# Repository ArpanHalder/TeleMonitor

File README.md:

# TeleMonitor
This Open Hardware initiative is focused mostly on industrial application. In fact, this started with designing a low-cost Telemonitoring system for Mining Industry Applications. It is an embedded data transmission setup made up on small Arduino like boards. For long distance communication between device nodes, it uses RS-485

![alt text][master_diag]

##Motivation
While working in the laboratory, our team did experiment similar thing using state of the art services. However, not every educational institute has access to premium facilities. This project is initiated to enable us (who have access to premium education) to build some full-scale copyleft open technology that can be used for demonstration of remote monitoring operation in academia as well as in industries.
(After the device, hopefully soon the projects for IDE of this instrument, and Open Source Analytics & Visualization tools for this project shall be published after development of first working prototype.)

##Design Approaches
One of the primary objectives is keeping the hardware cheap, straightforward and reparable. We don't want a design where if one component fails the whole circuit is replaced, which create extra junk on the surface of the earth.

###This Device is motivated by the idea of "Democratisation of Technology & Education."
<https://en.wikipedia.org/wiki/Democratization_of_technology>

<http://www.thehindu.com/news/national/andhra-pradesh/science-should-touch-lives-of-common-people/article8539013.ece>

This is why we wish to keep the design simple and affordable like DIY projects, however, rich with all necessary features. This we can hopefully achieve by the cognitive support of the community. We also suggest restricting use of components in the design that tier III nations cannot afford to import or implement in the industries. 

##Ways to Contribute in this project

Discuss the possible improvement, and feature requirements.

Contact : tech.halder.arpan@gmail.com

[master_diag]: https://github.com/ArpanHalder/TeleMonitor/blob/master/Hardware/Schimatics/Schematic%20Diagram%20V1.png

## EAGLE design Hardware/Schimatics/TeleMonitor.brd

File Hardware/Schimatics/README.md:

#Hardware Schematics for Telemonitoring nodes

![alt text][master_diag]

## How to Read/Open

The files are made with eagle cad. 

There are image files naming  *.PNG  

Currently Schematics is drawn in a way which can easily be implimented with one sided perforated board. (to avoid PCB printing cost for early developers.) 

**Please Note:** the top layer on PCB (the red streaks) need not to be solder bridged, rather a thin wire may be used which shall be soldered on bottom side.

![alt text][master_pcb]

### Current Job
~~Looking forward to make a vias less PCB that can be printed and fabricated manually.~~

~~On Veroboard~~

Add more necessary components and rearrangement for improvements. 

[master_diag]: https://github.com/ArpanHalder/TeleMonitor/blob/master/Hardware/Schimatics/Schematic%20Diagram%20V1.png

[master_pcb]: https://github.com/ArpanHalder/TeleMonitor/blob/master/Hardware/Schimatics/TeleMonitor%20PCB%20V1.png

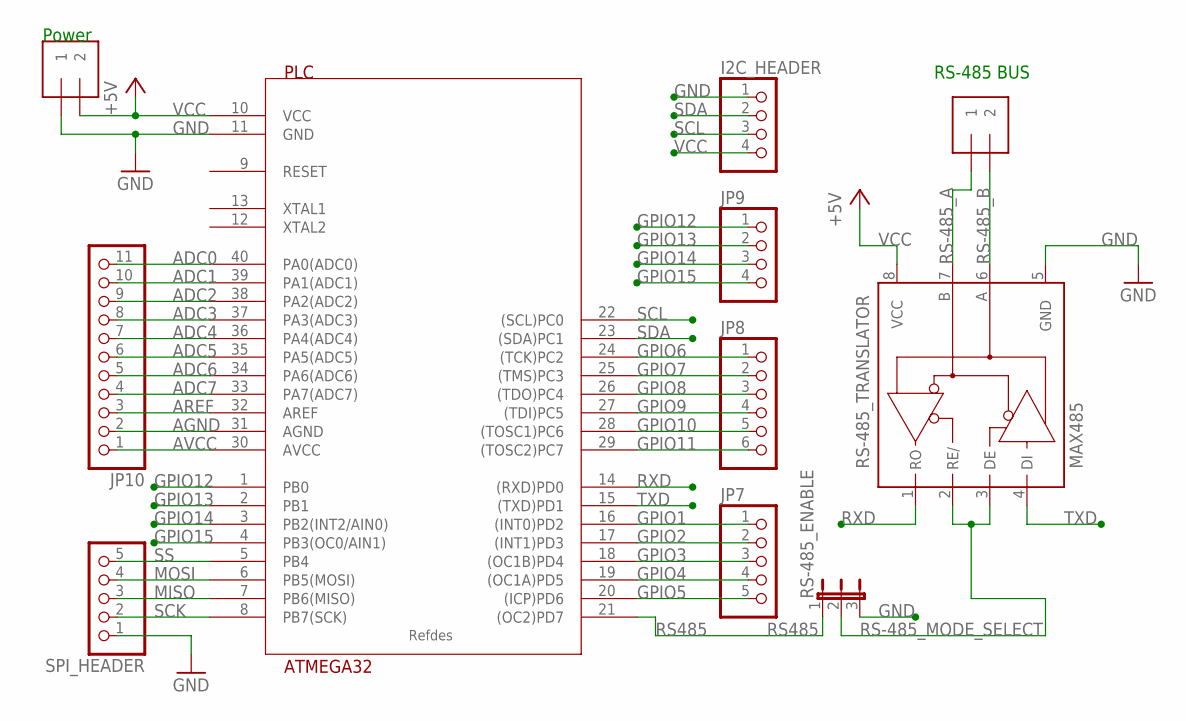
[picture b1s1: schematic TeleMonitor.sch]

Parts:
I2C_HEADER: PINHD-1X4; 1X04
JP7: PINHD-1X5; 1X05
JP8: PINHD-1X6; 1X06
JP9: PINHD-1X4; 1X04
JP10: PINHD-1X11; 1X11
PLC: ATMEGA32; DIL40
POWER: 5MM_TERMINAL_BLOCK-3.5MM; 1X2-3.5MM
RS-485: 5MM_TERMINAL_BLOCK-3.5MM; 1X2-3.5MM
RS-485_ENABLE: JP2E; JP2
RS-485_TRANSLATOR: MAX485; DIL08
SPI_HEADER: PINHD-1X5; 1X05

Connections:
ADC0: JP10.11, PLC.40 (PA0(ADC0))
ADC1: JP10.10, PLC.39 (PA1(ADC1))
ADC2: JP10.9, PLC.38 (PA2(ADC2))
ADC3: JP10.8, PLC.37 (PA3(ADC3))
ADC4: JP10.7, PLC.36 (PA4(ADC4))
ADC5: JP10.6, PLC.35 (PA5(ADC5))
ADC6: JP10.5, PLC.34 (PA6(ADC6))
ADC7: JP10.4, PLC.33 (PA7(ADC7))
AGND: JP10.2, PLC.31 (AGND)
AREF: JP10.3, PLC.32 (AREF)
AVCC: JP10.1, PLC.30 (AVCC)
GND: I2C_HEADER.1, PLC.11 (GND), POWER.1, RS-485_ENABLE.3, RS-485_TRANSLATOR.5 (GND), SPI_HEADER.1
GPIO1: JP7.1, PLC.16 ((INT0)PD2)
GPIO2: JP7.2, PLC.17 ((INT1)PD3)
GPIO3: JP7.3, PLC.18 ((OC1B)PD4)
GPIO4: JP7.4, PLC.19 ((OC1A)PD5)
GPIO5: JP7.5, PLC.20 ((ICP)PD6)
GPIO6: JP8.1, PLC.24 ((TCK)PC2)
GPIO7: JP8.2, PLC.25 ((TMS)PC3)
GPIO8: JP8.3, PLC.26 ((TDO)PC4)
GPIO9: JP8.4, PLC.27 ((TDI)PC5)
GPIO10: JP8.5, PLC.28 ((TOSC1)PC6)
GPIO11: JP8.6, PLC.29 ((TOSC2)PC7)
GPIO12: JP9.1, PLC.1 (PB0)
GPIO13: JP9.2, PLC.2 (PB1)
GPIO14: JP9.3, PLC.3 (PB2(INT2/AIN0))
GPIO15: JP9.4, PLC.4 (PB3(OC0/AIN1))
MISO: PLC.7 (PB6(MISO)), SPI_HEADER.3
MOSI: PLC.6 (PB5(MOSI)), SPI_HEADER.4
RS485: PLC.21 ((OC2)PD7), RS-485_ENABLE.1
RS-485_A: RS-485.1, RS-485_TRANSLATOR.7 (B)
RS-485_B: RS-485.2, RS-485_TRANSLATOR.6 (A)
RS-485_MODE_SELECT: RS-485_ENABLE.2, RS-485_TRANSLATOR.2 (RE/), RS-485_TRANSLATOR.3 (DE)
RXD: PLC.14 ((RXD)PD0), RS-485_TRANSLATOR.1 (RO)
SCK: PLC.8 (PB7(SCK)), SPI_HEADER.2
SCL: I2C_HEADER.3, PLC.22 ((SCL)PC0)
SDA: I2C_HEADER.2, PLC.23 ((SDA)PC1)
SS: PLC.5 (PB4), SPI_HEADER.5
TXD: PLC.15 ((TXD)PD1), RS-485_TRANSLATOR.4 (DI)
VCC: I2C_HEADER.4, PLC.10 (VCC), POWER.2, RS-485_TRANSLATOR.8 (VCC)

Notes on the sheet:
Power
RS-485 BUS

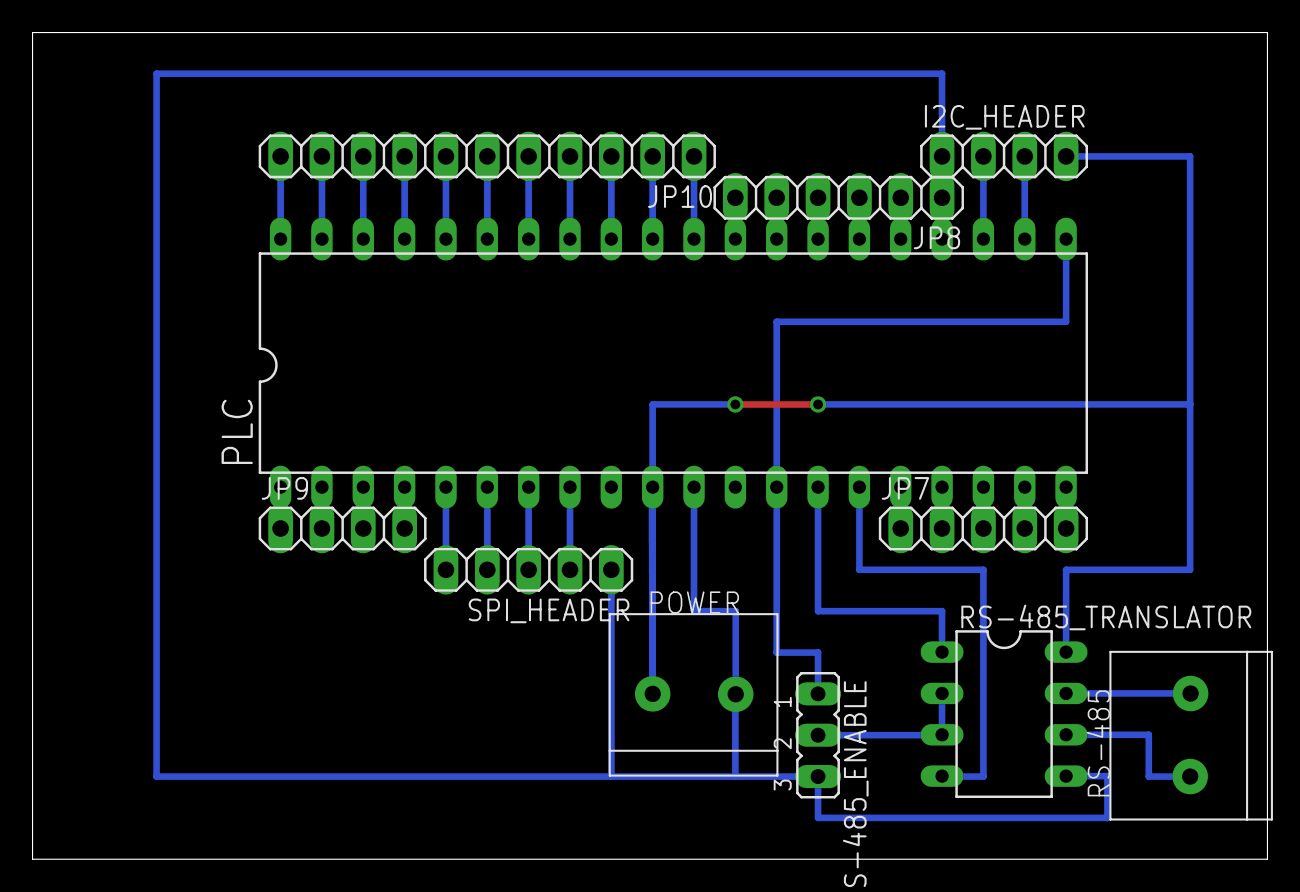
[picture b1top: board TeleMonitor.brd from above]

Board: 2 copper layers, 75.9 x 50.8 mm, 11 parts (0 on the bottom side), 40 nets.

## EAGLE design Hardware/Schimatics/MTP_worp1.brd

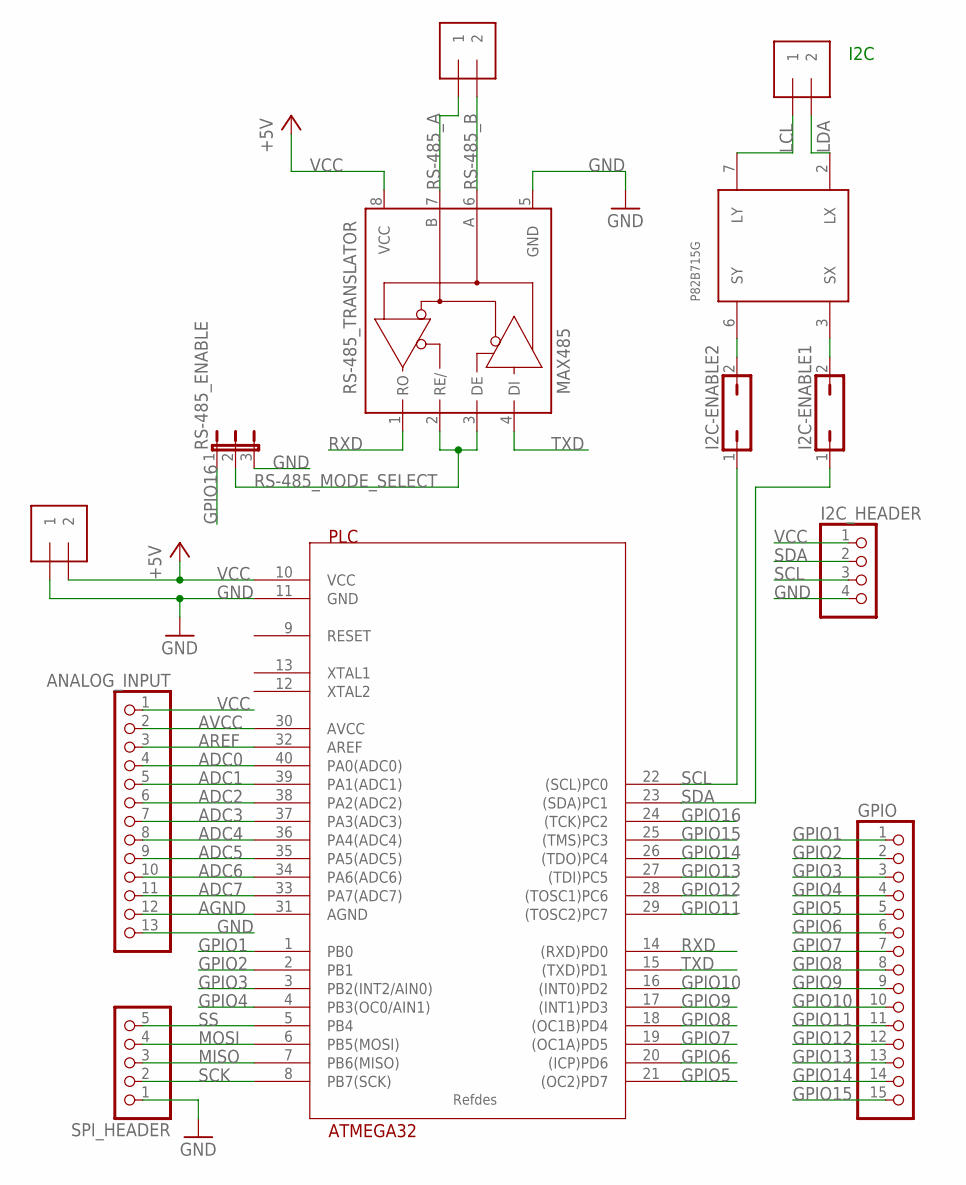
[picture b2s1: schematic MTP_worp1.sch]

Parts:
ANALOG_INPUT: PINHD-1X13; 1X13
GPIO: PINHD-1X15-CB; 1X15-CB
I2C: 1X2-3.5MM
I2C-ENABLE1, I2C-ENABLE2: JP1Q; JP1
I2C_HEADER: PINHD-1X4; 1X04
P82B715: 82B715TD; SO8
PLC: ATMEGA32; DIP254P1524X482-40
POWER: 1X2-3.5MM
RS-485: 1X2-3.5MM
RS-485_ENABLE: JP2E; JP2
RS-485_TRANSLATOR: MAX485; DIL08
SPI_HEADER: PINHD-1X5; 1X05

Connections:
ADC0: ANALOG_INPUT.4, PLC.40 (PA0(ADC0))
ADC1: ANALOG_INPUT.5, PLC.39 (PA1(ADC1))
ADC2: ANALOG_INPUT.6, PLC.38 (PA2(ADC2))
ADC3: ANALOG_INPUT.7, PLC.37 (PA3(ADC3))
ADC4: ANALOG_INPUT.8, PLC.36 (PA4(ADC4))
ADC5: ANALOG_INPUT.9, PLC.35 (PA5(ADC5))
ADC6: ANALOG_INPUT.10, PLC.34 (PA6(ADC6))
ADC7: ANALOG_INPUT.11, PLC.33 (PA7(ADC7))
AGND: ANALOG_INPUT.12, PLC.31 (AGND)
AREF: ANALOG_INPUT.3, PLC.32 (AREF)
AVCC: ANALOG_INPUT.2, PLC.30 (AVCC)
GND: ANALOG_INPUT.13, I2C_HEADER.4, PLC.11 (GND), POWER.1, RS-485_ENABLE.3, RS-485_TRANSLATOR.5 (GND), SPI_HEADER.1; also elsewhere on the board
GPIO1: GPIO.1, PLC.1 (PB0)
GPIO2: GPIO.2, PLC.2 (PB1)
GPIO3: GPIO.3, PLC.3 (PB2(INT2/AIN0))
GPIO4: GPIO.4, PLC.4 (PB3(OC0/AIN1))
GPIO5: GPIO.5, PLC.21 ((OC2)PD7)
GPIO6: GPIO.6, PLC.20 ((ICP)PD6)
GPIO7: GPIO.7, PLC.19 ((OC1A)PD5)
GPIO8: GPIO.8, PLC.18 ((OC1B)PD4)
GPIO9: GPIO.9, PLC.17 ((INT1)PD3)
GPIO10: GPIO.10, PLC.16 ((INT0)PD2)
GPIO11: GPIO.11, PLC.29 ((TOSC2)PC7)
GPIO12: GPIO.12, PLC.28 ((TOSC1)PC6)
GPIO13: GPIO.13, PLC.27 ((TDI)PC5)
GPIO14: GPIO.14, PLC.26 ((TDO)PC4)
GPIO15: GPIO.15, PLC.25 ((TMS)PC3)
GPIO16: PLC.24 ((TCK)PC2), RS-485_ENABLE.1
LCL: I2C.1, P82B715.7 (LY); also elsewhere on the board
LDA: I2C.2, P82B715.2 (LX); also elsewhere on the board
MISO: PLC.7 (PB6(MISO)), SPI_HEADER.3
MOSI: PLC.6 (PB5(MOSI)), SPI_HEADER.4
unnamed 32: I2C-ENABLE2.2, P82B715.6 (SY); also elsewhere on the board
unnamed 33: I2C-ENABLE1.2, P82B715.3 (SX); also elsewhere on the board
RS-485_A: RS-485.1, RS-485_TRANSLATOR.7 (B)
RS-485_B: RS-485.2, RS-485_TRANSLATOR.6 (A)
RS-485_MODE_SELECT: RS-485_ENABLE.2, RS-485_TRANSLATOR.2 (RE/), RS-485_TRANSLATOR.3 (DE)
RXD: PLC.14 ((RXD)PD0), RS-485_TRANSLATOR.1 (RO)
SCK: PLC.8 (PB7(SCK)), SPI_HEADER.2
SCL: I2C-ENABLE2.1, I2C_HEADER.3, PLC.22 ((SCL)PC0)
SDA: I2C-ENABLE1.1, I2C_HEADER.2, PLC.23 ((SDA)PC1)
SS: PLC.5 (PB4), SPI_HEADER.5
TXD: PLC.15 ((TXD)PD1), RS-485_TRANSLATOR.4 (DI)
VCC: ANALOG_INPUT.1, I2C_HEADER.1, PLC.10 (VCC), POWER.2, RS-485_TRANSLATOR.8 (VCC); also elsewhere on the board

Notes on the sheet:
I2C

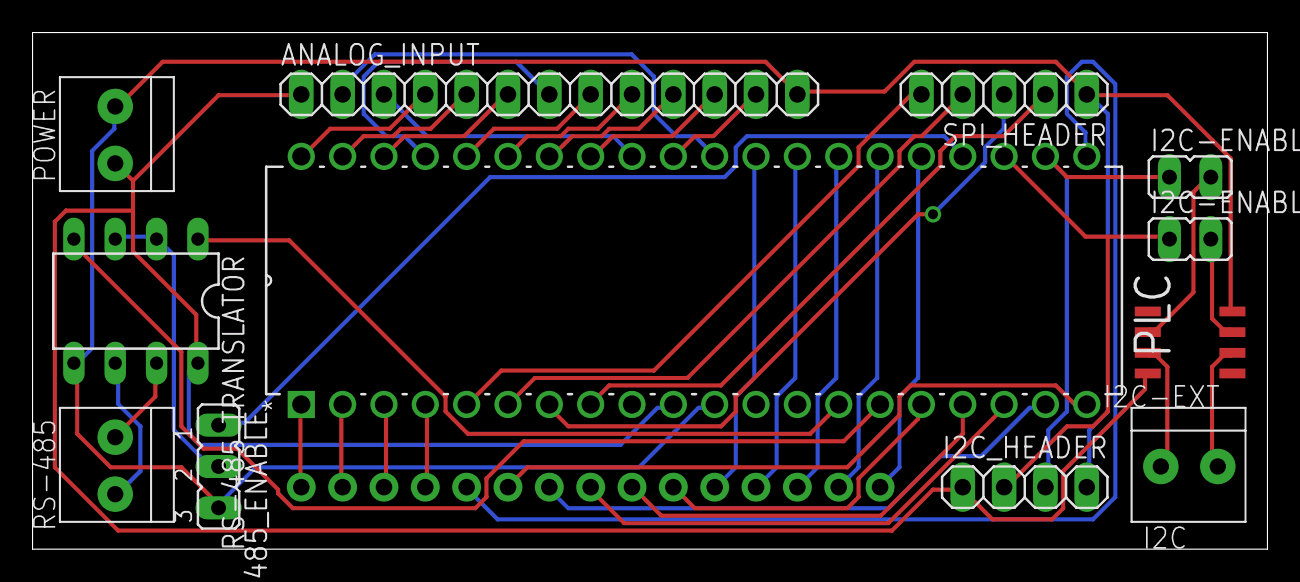
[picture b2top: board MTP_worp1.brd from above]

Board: 2 copper layers, 75.9 x 31.7 mm, 13 parts (0 on the bottom side), 44 nets.

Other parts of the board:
I2C-EXT: P82B715; SO8

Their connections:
GND: I2C-EXT.4; also elsewhere on the board
LCL: I2C-EXT.7; also elsewhere on the board
LDA: I2C-EXT.2; also elsewhere on the board
unnamed 32: I2C-EXT.6; also elsewhere on the board
unnamed 33: I2C-EXT.3; also elsewhere on the board
VCC: I2C-EXT.8; also elsewhere on the board

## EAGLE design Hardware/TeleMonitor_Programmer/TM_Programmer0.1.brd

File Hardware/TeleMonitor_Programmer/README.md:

# This is Programmer for TeleMonitor MCUs
Preferably this can also be done in breadboard. With Arduino IDE via Arduino as ISP or any other AVR HEX uploader.
## Please note: The top layer (marked as red) needn't to be printed, they are preferably connected manually by means of insulated wires.

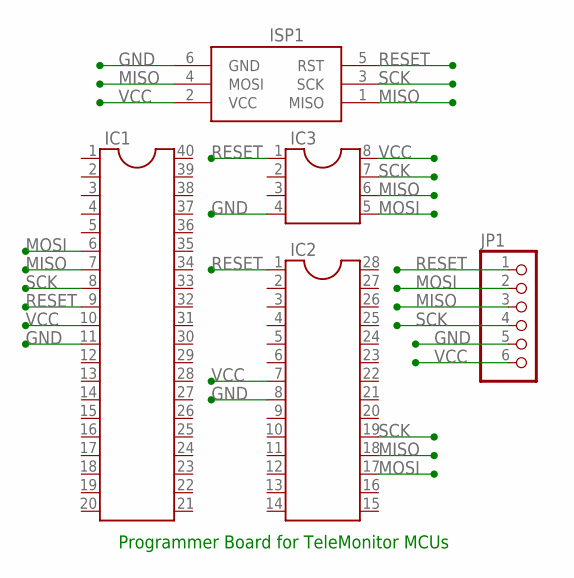
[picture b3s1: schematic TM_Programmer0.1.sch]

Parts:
IC1: DIL40
IC2: DIL28-3
IC3: DIL8S; SOCKET-08
ISP1: AVRISP-6; AVRISP
JP1: PINHD-1X6; 1X06

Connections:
GND: IC1.11, IC2.8, IC3.4, ISP1.6 (GND), JP1.5
MISO: IC1.7, IC2.18, IC3.6, ISP1.1 (MISO), ISP1.4 (MOSI), JP1.3
MOSI: IC1.6, IC2.17, IC3.5, JP1.2
RESET: IC1.9, IC2.1, IC3.1, ISP1.5 (RST), JP1.1
SCK: IC1.8, IC2.19, IC3.7, ISP1.3 (SCK), JP1.4
VCC: IC1.10, IC2.7, IC3.8, ISP1.2 (VCC), JP1.6

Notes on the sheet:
Programmer Board for TeleMonitor MCUs

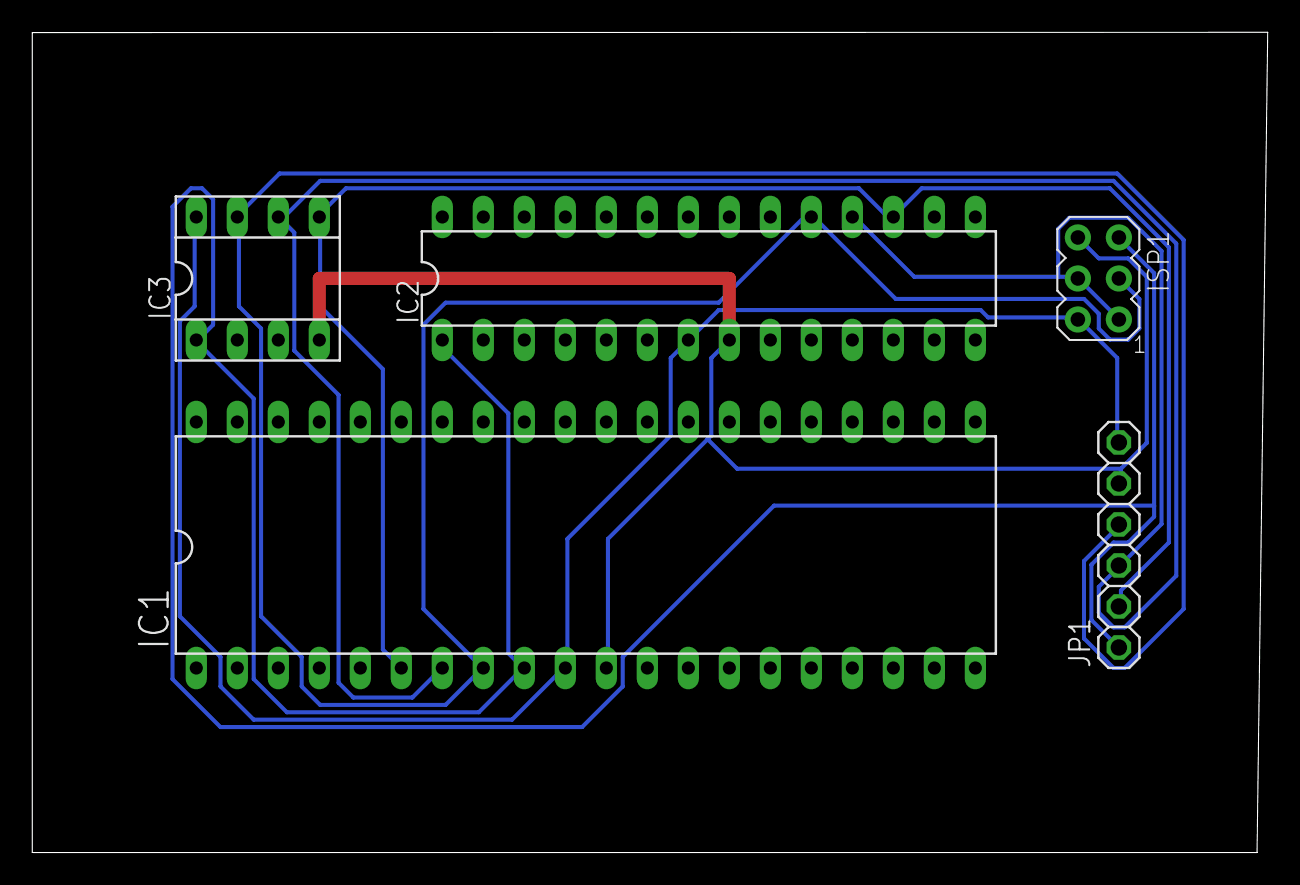
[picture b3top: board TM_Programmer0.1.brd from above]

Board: 2 copper layers, 76.5 x 50.8 mm, 5 parts (0 on the bottom side), 6 nets.

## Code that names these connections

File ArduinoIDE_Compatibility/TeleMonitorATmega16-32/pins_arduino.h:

/*
    Author:		Arpah Halder, Department of Mining Engineering, IIT Kharagpur
	Email:		tech.halder.arpan@gmail.com
	Date:		21-05-2016
	Project:	TeleMonitor
 	Version:	v1.0
	
	Inspired by Eric Conner's ATmega32 for Arduino IDE project
*/

#ifndef Pins_Arduino_h
#define Pins_Arduino_h

#include <avr/pgmspace.h>

#define NOT_ON_TIMER 0
#define TIMER0A 1
#define TIMER0B 2
#define TIMER1A 3
#define TIMER1B 4
#define TIMER2  5

#undef TCCR2A

#define NOT_A_PORT 0
#define NOT_ON_TIMER 0

/*			
		                             ATMEL ATmega16-32			
					
                                      + - - U - - +                                  
            GPIO  12    PB  0     1   |           |   40    PA  0   ADC 0   GPIO  20
            GPIO  13    PB  1     2   |           |   39    PA  1   ADC 1   GPIO  21
            GPIO  14    PB  2     3   |           |   38    PA  2   ADC 2   GPIO  22
            GPIO  15    PB  3     4   |           |   37    PA  3   ADC 3   GPIO  23
    SS      GPIO  16    PB  4     5   |           |   36    PA  4   ADC 4   GPIO  24
  MOSI      GPIO  17    PB  5     6   |           |   35    PA  5   ADC 5   GPIO  25
  MISO      GPIO  18    PB  6     7   |           |   34    PA  6   ADC 6   GPIO  26
   SCK      GPIO  19    PB  7     8   |           |   33    PA  7   ADC 7   GPIO  27
 RESET                            9   |           |   32            AREF             
   VCC                           10   |           |   31            GND              
   GND                           11   |           |   30            AVCC             
 XTAL2                           12   |           |   29    PC  7           GPIO  11
 XTAL1                           13   |           |   28    PC  6           GPIO  10
   RXD                  PD  0    14   |           |   27    PC  5           GPIO  9
   TXD                  PD  1    15   |           |   26    PC  4           GPIO  8
            GPIO  1     PD  2    16   |           |   25    PC  3           GPIO  7
            GPIO  2     PD  3    17   |           |   24    PC  2           GPIO  6
            GPIO  3     PD  4    18   |           |   23    PC  1   SDA     GPIO  28
            GPIO  4     PD  5    19   |           |   22    PC  0   SCL     GPIO  29
            GPIO  5     PD  6    20   |           |   21    PD  7   RS-485  GPIO  30
                                      + - - - - - +                        
*/			


const static uint8_t SDA = 28;
const static uint8_t SCL = 29;

const static uint8_t SS   = 16;
const static uint8_t MOSI = 17;
const static uint8_t MISO = 18;
const static uint8_t SCK  = 19;

static const uint8_t A0 = 0;
static const uint8_t A1 = 1;
static const uint8_t A2 = 2;
static const uint8_t A3 = 3;
static const uint8_t A4 = 4;
static const uint8_t A5 = 5;
static const uint8_t A6 = 6;
static const uint8_t A7 = 7;

#define NUM_DIGITAL_PINS            32
#define NUM_ANALOG_INPUTS           8
#define analogInputToDigitalPin(p)  ((p < 8) ? (p) + 24 : -1)//TODO : MAPPING
#define digitalPinHasPWM(p)         ((p) == 4 || (p) == 5 || (p) == 7) //TODO: MPPING

#ifdef ARDUINO_MAIN

const uint16_t PROGMEM port_to_mode_PGM[] = {
	NOT_A_PORT,
	(uint16_t) &DDRA,
	(uint16_t) &DDRB,
	(uint16_t) &DDRC,
	(uint16_t) &DDRD,
	NOT_A_PORT,
	NOT_A_PORT,
};

const uint16_t PROGMEM port_to_output_PGM[] = {
	NOT_A_PORT,
	(uint16_t) &PORTA,
	(uint16_t) &PORTB,
	(uint16_t) &PORTC,
	(uint16_t) &PORTD,
	NOT_A_PORT,
	NOT_A_PORT,
};

const uint16_t PROGMEM port_to_input_PGM[] = {
	NOT_A_PORT,
	(uint16_t) &PINA,
	(uint16_t) &PINB,
	(uint16_t) &PINC,
	(uint16_t) &PIND,
	NOT_A_PORT,
	NOT_A_PORT,
};

const uint8_t PROGMEM digital_pin_to_port_PGM[30] = {
PD	,	 	 //	 	PD2	 	>>>	GPIO		1
PD	,	 	 //	 	PD3	 	>>>	GPIO		2
PD	,	 	 //	 	PD4	 	>>>	GPIO		3
PD	,	 	 //	 	PD5	 	>>>	GPIO		4
PD	,	 	 //	 	PD6	 	>>>	GPIO		5
PC	,	 	 //	 	PC2	 	>>>	GPIO		6
PC	,	 	 //	 	PC3	 	>>>	GPIO		7
PC	,	 	 //	 	PC4	 	>>>	GPIO		8
PC	,	 	 //	 	PC5	 	>>>	GPIO		9
PC	,	 	 //	 	PC6	 	>>>	GPIO	    10
PC	,	 	 //	 	PC7	 	>>>	GPIO		11
PB	,	 	 //	 	PB0	 	>>>	GPIO    	12
PB	,	 	 //	 	PB1	 	>>>	GPIO 		13
PB	,	 	 //	 	PB2	 	>>>	GPIO 		14
PB	,	 	 //	 	PB3	 	>>>	GPIO 		15
PB	,	 	 //	 	PB4	 	>>>	GPIO		16
PB	,	 	 //	 	PB5	 	>>>	GPIO		17
PB	,	 	 //	 	PB6	 	>>>	GPIO		18
PB	,	 	 //	 	PB7	 	>>>	GPIO		19
PA	,	 	 //	 	PA0	 	>>>	GPIO		20
PA	,	 	 //	 	PA1	 	>>>	GPIO		21
PA	,	 	 //	 	PA2	 	>>>	GPIO		22
PA	,	 	 //	 	PA3	 	>>>	GPIO		23
PA	,	 	 //	 	PA4	 	>>>	GPIO		24
PA	,	 	 //	 	PA5	 	>>>	GPIO		25
PA	,	 	 //	 	PA6	 	>>>	GPIO		26
PA	,	 	 //	 	PA7	 	>>>	GPIO		27
PC	,	 	 //	 	PC1	 	>>>	GPIO		28
PC	,	 	 //	 	PC0	 	>>>	GPIO		29
PD	,	 	 //	 	PD7	 	>>>	GPIO		30
};

const uint8_t PROGMEM digital_pin_to_bit_mask_PGM[30] = {	
_BV(2),	 	 //	 	PD	2	 	>>>	GPIO		1
_BV(3),	 	 //	 	PD	3	 	>>>	GPIO		2
_BV(4),	 	 //	 	PD	4	 	>>>	GPIO		3
_BV(5),	 	 //	 	PD	5	 	>>>	GPIO		4
_BV(6),	 	 //	 	PD	6	 	>>>	GPIO		5
_BV(2),	 	 //	 	PC	2	 	>>>	GPIO		6
_BV(3),	 	 //	 	PC	3	 	>>>	GPIO		7
_BV(4),	 	 //	 	PC	4	 	>>>	GPIO		8
_BV(5),	 	 //	 	PC	5	 	>>>	GPIO		9
_BV(6),	 	 //	 	PC	6	 	>>>	GPIO	 10
_BV(7),	 	 //	 	PC	7	 	>>>	GPIO	 11
_BV(0),	 	 //	 	PB	0	 	>>>	GPIO	 12
_BV(1),	 	 //	 	PB	1	 	>>>	GPIO	 13
_BV(2),	 	 //	 	PB	2	 	>>>	GPIO	 14
_BV(3),	 	 //	 	PB	3	 	>>>	GPIO	 15
_BV(4),	 	 //	 	PB	4	 	>>>	GPIO	 16
_BV(5),	 	 //	 	PB	5	 	>>>	GPIO	 17
_BV(6),	 	 //	 	PB	6	 	>>>	GPIO	 18
_BV(7),	 	 //	 	PB	7	 	>>>	GPIO	 19
_BV(0),	 	 //	 	PA	0	 	>>>	GPIO	 20
_BV(1),	 	 //	 	PA	1	 	>>>	GPIO	 21
_BV(2),	 	 //	 	PA	2	 	>>>	GPIO	 22
_BV(3),	 	 //	 	PA	3	 	>>>	GPIO	 23
_BV(4),	 	 //	 	PA	4	 	>>>	GPIO	 24
_BV(5),	 	 //	 	PA	5	 	>>>	GPIO	 25
_BV(6),	 	 //	 	PA	6	 	>>>	GPIO	 26
_BV(7),	 	 //	 	PA	7	 	>>>	GPIO	 27
_BV(1),	 	 //	 	PC	1	 	>>>	GPIO	 28
_BV(0),	 	 //	 	PC	0	 	>>>	GPIO	 29
_BV(7),	 	 //	 	PD	7	 	>>>	GPIO	 30
};
//TODO: TIMER MAPPING
const uint8_t PROGMEM digital_pin_to_timer_PGM[32] = {
	NOT_ON_TIMER,  // PB0 ** D0
	NOT_ON_TIMER,  // PB1 ** D1
	NOT_ON_TIMER,  // PB2 ** D2
	TIMER0A,	   // PB3 ** D3
	NOT_ON_TIMER,  // PB4 ** D4
	NOT_ON_TIMER,  // PB5 ** D5
	NOT_ON_TIMER,  // PB6 ** D6
	NOT_ON_TIMER,  // PB7 ** D7
	NOT_ON_TIMER,  // PD0 ** D8
	NOT_ON_TIMER,  // PD1 ** D9
	NOT_ON_TIMER,  // PD2 ** D10
	NOT_ON_TIMER,  // PD3 ** D11
	TIMER1B,	   // PD4 ** D12
	TIMER1A,	   // PD5 ** D13
	NOT_ON_TIMER,  // PD6 ** D14
	TIMER2,		   // PD7 ** D15
	NOT_ON_TIMER,  // PC0 ** D16
	NOT_ON_TIMER,  // PC1 ** D17
	NOT_ON_TIMER,  // PC2 ** D18
	NOT_ON_TIMER,  // PC3 ** D19
	NOT_ON_TIMER,  // PC4 ** D20
	NOT_ON_TIMER,  // PC5 ** D21
	NOT_ON_TIMER,  // PC6 ** D22
	NOT_ON_TIMER,  // PC7 ** D23
	NOT_ON_TIMER,  // PA7 ** A0 D24
	NOT_ON_TIMER,  // PA6 ** A1 D25
	NOT_ON_TIMER,  // PA5 ** A2 D26
	NOT_ON_TIMER,  // PA4 ** A3 D27
	NOT_ON_TIMER,  // PA3 ** A4 D28
	NOT_ON_TIMER,  // PA2 ** A5 D29
	NOT_ON_TIMER,  // PA1 ** A6 D30
	NOT_ON_TIMER,  // PA0 ** A7 D31
};

#endif
#endif

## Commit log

2016-05-03 Schimatics uploaded
2016-05-03 The PNG file of Diagram Uploaded
2016-05-04 for TeleMonitor Programmer
2016-05-05 Programmer Schematics Uploaded
2016-05-07 test of
    testing the correction
2016-05-19 Git ignore for desktop.iini
2016-05-19 Simplified Schematics:
    That can be implimented with standard 3x2 in veroboards. this is to avoid PCB printing costs.
2016-05-19 Update on 19th may
2016-05-19 V 1.0 diag
2016-05-19 real stuff
2016-05-19 PCB diagrams uploaded
2016-05-21 Updating arduino ide Compatiability contents
2016-05-22 Just a minor folder move. Put the compatiability file outside hardware folder
2016-05-23 Updated all readme's
2016-05-23 Readme of Schematics
2016-05-23 uploaded Sche edits
2016-05-23 readme
2016-05-31 readme update with diagram
2016-06-08 pic of pin playout atmega 40 pin added
2016-06-10 documentation June
2016-06-10 fix the sync issue
2016-06-10 markdown
